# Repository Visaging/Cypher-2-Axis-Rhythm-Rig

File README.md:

# Cypher - 2 Axis Rhythm Rig
# TBA

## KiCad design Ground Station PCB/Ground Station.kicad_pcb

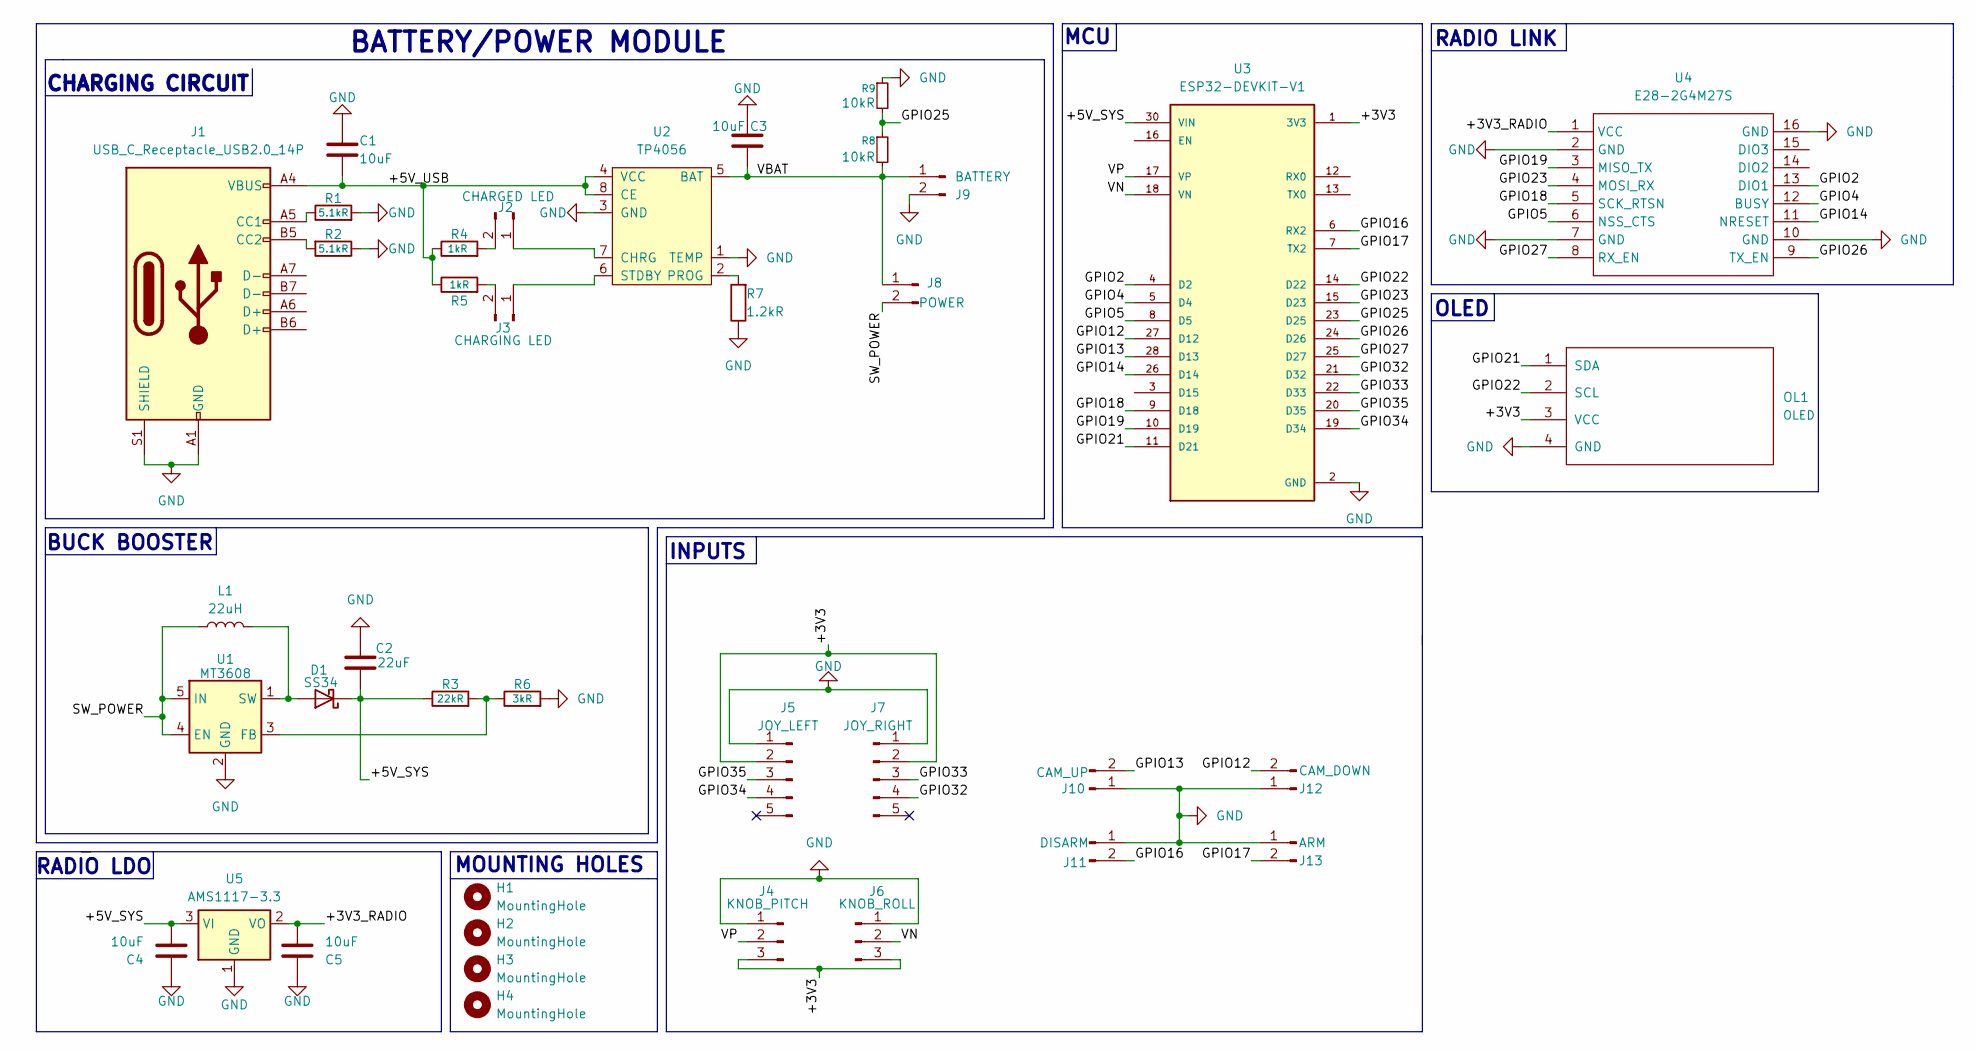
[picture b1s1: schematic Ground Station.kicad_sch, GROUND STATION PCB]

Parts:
C1, C4, C5: 10uF; C_0805_2012Metric
C2: 22uF; C_0805_2012Metric
C3: 10uF; CP_Radial_D5.0mm_P2.50mm
D1: SS34; D_SMA
H1, H2, H3, H4: MountingHole; MountingHole_3.2mm_M3
J1: USB_C_Receptacle_USB2.0_14P; USB_C_Receptacle_HRO_TYPE-C-31-M-12
J2: CHARGED LED; SolderWire-0.1sqmm_1x02_P3.6mm_D0.4mm_OD1mm
J3: CHARGING LED; SolderWire-0.1sqmm_1x02_P3.6mm_D0.4mm_OD1mm
J4: KNOB_PITCH; PinHeader_1x03_P2.54mm_Vertical
J5: JOY_LEFT; PinHeader_1x05_P2.54mm_Vertical
J6: KNOB_ROLL; PinHeader_1x03_P2.54mm_Vertical
J7: JOY_RIGHT; PinHeader_1x05_P2.54mm_Vertical
J8: POWER; PinHeader_1x02_P2.54mm_Vertical
J9: BATTERY; PinHeader_1x02_P2.54mm_Vertical
J10: CAM_UP; SolderWire-0.1sqmm_1x02_P3.6mm_D0.4mm_OD1mm
J11: DISARM; SolderWire-0.1sqmm_1x02_P3.6mm_D0.4mm_OD1mm
J12: CAM_DOWN; SolderWire-0.1sqmm_1x02_P3.6mm_D0.4mm_OD1mm
J13: ARM; SolderWire-0.1sqmm_1x02_P3.6mm_D0.4mm_OD1mm
L1: 22uH; L_Bourns-SRN6028
OL1: OLED; PinHeader_1x04_P2.54mm_Vertical
R1, R2: 5.1kR; R_0805_2012Metric
R3: 22kR; R_0805_2012Metric
R4, R5: 1kR; R_0805_2012Metric
R6: 3kR; R_0805_2012Metric
R7: 1.2kR; R_0805_2012Metric
R8, R9: 10kR; R_0805_2012Metric
U1: MT3608; SOP-8-1EP_4.57x4.57mm_P1.27mm_EP4.57x4.45mm
U2: TP4056; SOIC-8-1EP_3.9x4.9mm_P1.27mm_EP2.29x3mm; LCSC C16581
U3: ESP32-DEVKIT-V1; MODULE_ESP32_DEVKIT_V1; PARTREV N/A
U4: E28-2G4M27S; WIRELM-SMD_E28-2G4M2XS; Manufacturer Part E28-2G4M27S; LCSC Part Name E28-2G4M27S
U5: AMS1117-3.3; SOT-223-3_TabPin2

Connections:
/+3V3: J4.3, J5.2, J6.3, J7.2, OL1.3 (VCC), U3.1 (3V3)
/+3V3_RADIO: C5.2, U4.1 (VCC), U5.2 (VO)
/+5V_SYS: C2.2, C4.2, D1.1 (K), R3.1, U3.30 (VIN), U5.3 (VI)
/+5V_USB: C1.2, J1.A4 (VBUS), J1.A9 (VBUS), J1.B4 (VBUS), J1.B9 (VBUS), R4.1, R5.1, U2.4 (VCC), U2.8 (CE)
/GPIO2: U3.4 (D2), U4.13 (DIO1)
/GPIO4: U3.5 (D4), U4.12 (BUSY)
/GPIO5: U3.8 (D5), U4.6 (NSS_CTS)
/GPIO12: J12.2, U3.27 (D12)
/GPIO13: J10.2, U3.28 (D13)
/GPIO14: U3.26 (D14), U4.11 (NRESET)
/GPIO16: J11.2, U3.6 (RX2)
/GPIO17: J13.2, U3.7 (TX2)
/GPIO18: U3.9 (D18), U4.5 (SCK_RTSN)
/GPIO19: U3.10 (D19), U4.3 (MISO_TX)
/GPIO21: OL1.1 (SDA), U3.11 (D21)
/GPIO22: OL1.2 (SCL), U3.14 (D22)
/GPIO23: U3.15 (D23), U4.4 (MOSI_RX)
/GPIO25: R8.1, R9.2, U3.23 (D25)
/GPIO26: U3.24 (D26), U4.9 (TX_EN)
/GPIO27: U3.25 (D27), U4.8 (RX_EN)
/GPIO32: J7.4, U3.21 (D32)
/GPIO33: J7.3, U3.22 (D33)
/GPIO34: J5.4, U3.19 (D34)
/GPIO35: J5.3, U3.20 (D35)
/SW_POWER: J8.2, L1.1, U1.4 (EN), U1.5 (IN)
/VBAT: C3.2, J8.1, J9.1, R8.2, U2.5 (BAT)
/VN: J6.2, U3.18 (VN)
/VP: J4.2, U3.17 (VP)
GND: C1.1, C2.1, C3.1, C4.1, C5.1, J1.A1 (GND), J1.A12 (GND), J1.B1 (GND), J1.B12 (GND), J1.S1 (SHIELD), J4.1, J5.1, J6.1, J7.1, J9.2, J10.1, J11.1, J12.1, J13.1, OL1.4 (GND), R1.2, R2.1, R6.2, R7.1, R9.1, U1.2 (GND), U2.1 (TEMP), U2.3 (GND), U3.2 (GND), U3.29 (GND), U4.2 (GND), U4.7 (GND), U4.10 (GND), U4.16 (GND), U5.1 (GND)
unnamed: D1.2 (A), L1.2, U1.1 (SW)
unnamed: J1.A5 (CC1), R1.1
unnamed: J1.B5 (CC2), R2.2
unnamed: J2.1, U2.7 (CHRG)
unnamed: J2.2, R4.2
unnamed: J3.1, U2.6 (STDBY)
unnamed: J3.2, R5.2
unnamed: R3.2, R6.1, U1.3 (FB)
unnamed: R7.2, U2.2 (PROG)

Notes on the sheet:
MCU
OLED
INPUTS
CHARGING CIRCUIT
MOUNTING HOLES
RADIO LINK
BATTERY/POWER MODULE
BUCK BOOSTER
RADIO LDO

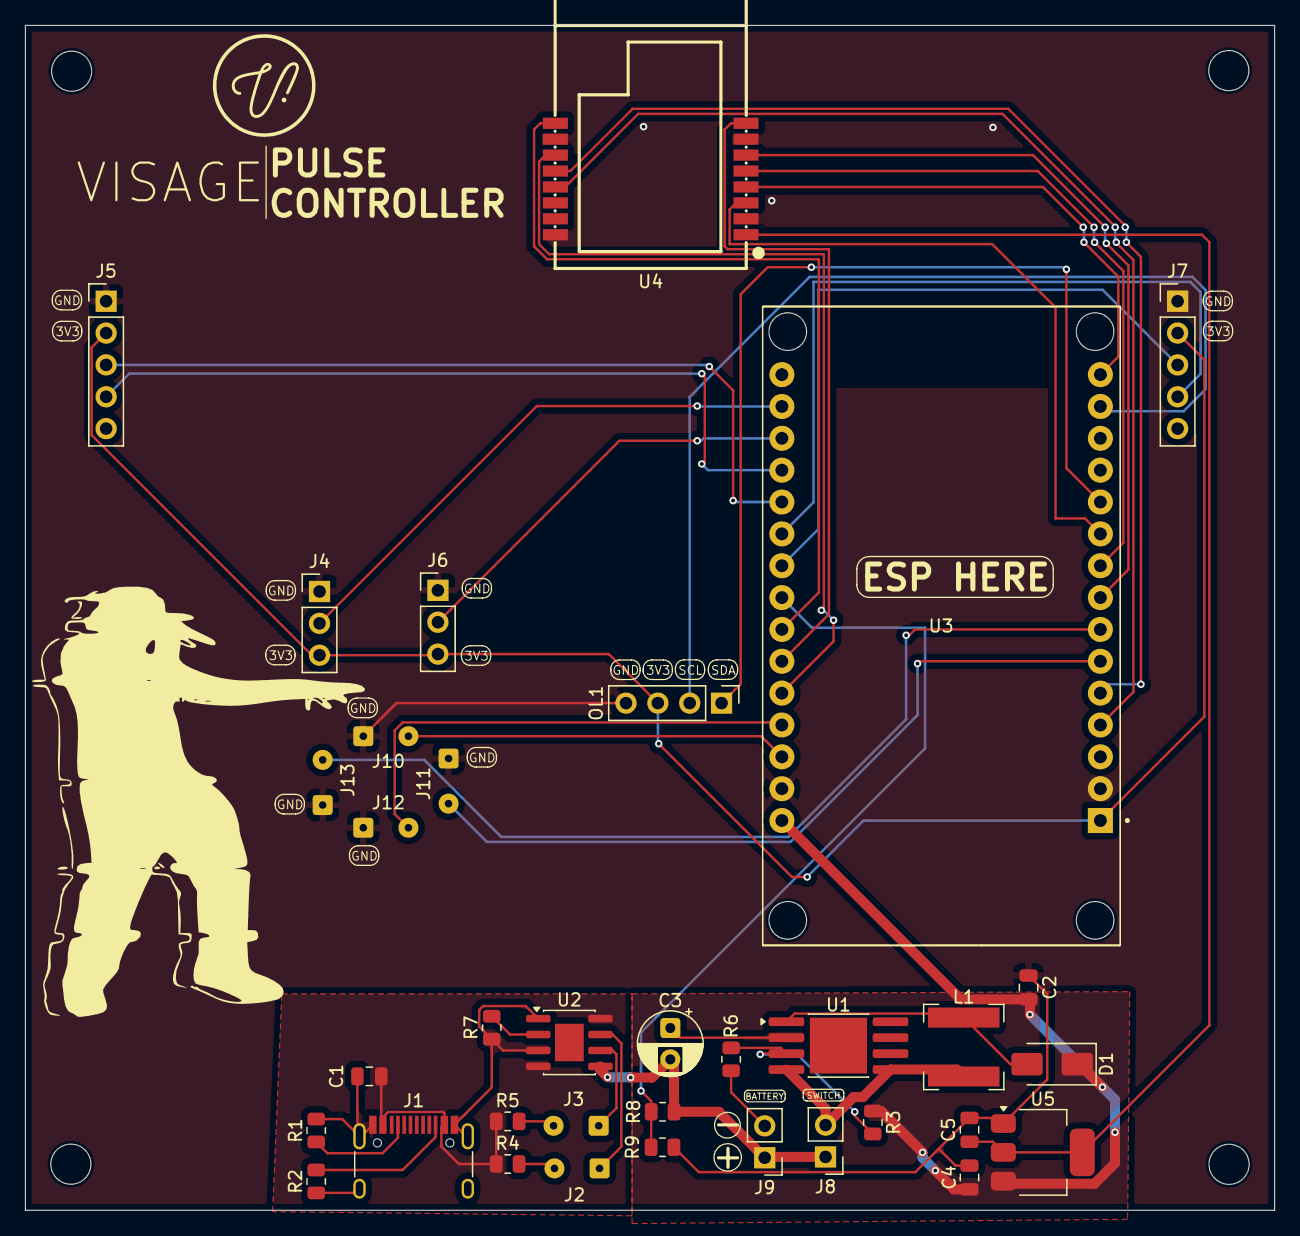
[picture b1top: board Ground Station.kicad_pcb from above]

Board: 2 copper layers, 99.6 x 94.5 mm, 39 parts (0 on the bottom side), 38 nets.

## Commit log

2026-02-19 Create a
2026-02-19 Rename a to TBA
2026-02-19 Create TBA
